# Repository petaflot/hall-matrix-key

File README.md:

# Hall Jumper Selector Matrix

A tool to help getting the configuration of hall sensors correct for any arbitrary 3-phase electric motor fitted with such devices. There are 6 possible arrangements, for direct and inverse rotations, and shifts relative to the phases. A 2x04 matrix is sufficient to select each arrangement by connecting adjacent pins.

A document that gives [more information on the arrangements](hall-jumper-matrix.pdf) can be found here.

## Hall Key

A simple yet elaborate mechanical device to ease the task of finding the correct jumper configuration ; special care was taken to reduce wear on the sliding contacts and thus extend the device life.
It looks pretty and is a somewhat mystical object that you can carry around everywhere you go.

***NOTE: In the above picture, the tracks are wrong ; this was fixed***

Datasheets of the required components are included.

### Note on the circular tracks

Considering the electrical and mechanical constraints, there is a unique solution to the arrangement ; therefore, it can be considered as a rune.

## Hall Matrix

A 2x04 pins jumper configuration matrix ; this project also includes a dedicated a solder jumper matrix footprint for Kicad. The pogo pins of the selector key go there, and they can be soldered once the correct configuration has been found.

***WARNING: footprint is not up-to-date with latest version of key!***

To ensure it can be accessed with the key, this footprint should go at the edge of the board.

An alternative is to use 2x04 header pins and regular jumpers ; this enables the configuration to be changed easily afterwards. In the case, connect to the key with a short cable.

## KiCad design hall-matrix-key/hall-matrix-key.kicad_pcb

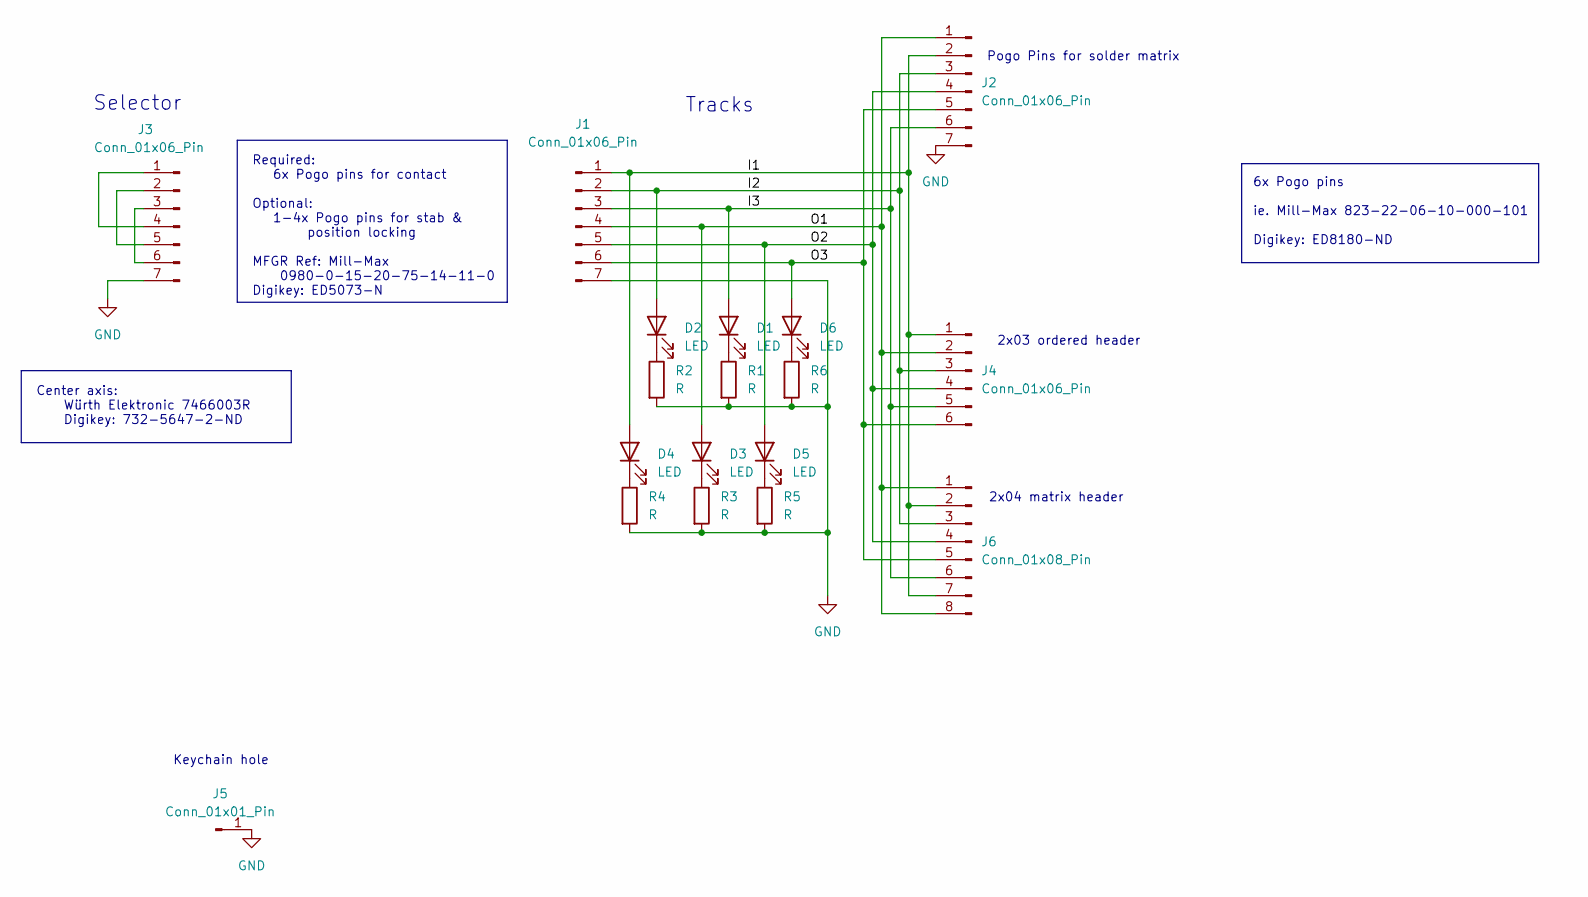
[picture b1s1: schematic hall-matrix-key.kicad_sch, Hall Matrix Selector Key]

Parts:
D1, D2, D3, D4, D5, D6: LED; LED_LiteOn_LTST-S326
J1: Conn_01x06_Pin; hall-matrix-selector-switch_base
J2: Conn_01x06_Pin; hall-matrix-selector_pogo
J3: Conn_01x06_Pin; hall-matrix-selector-switch_knob
J4: Conn_01x06_Pin; PinHeader_2x03_P2.54mm_Vertical
J5: Conn_01x01_Pin; keyhole
J6: Conn_01x08_Pin; PinHeader_2x04_P2.54mm_Vertical
R1, R2, R3, R4, R5, R6: R; R_0805_2012Metric_Pad1.20x1.40mm_HandSolder

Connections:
/I1: D4.2 (A), J1.1, J2.2, J4.1, J6.2, J6.7
/I2: D2.2 (A), J1.2, J2.3, J4.3, J6.3
/I3: D1.2 (A), J1.3, J2.6, J4.5, J6.6
/O1: D3.2 (A), J1.4, J2.1, J4.2, J6.1, J6.8
/O2: D5.2 (A), J1.5, J2.4, J4.4, J6.4
/O3: D6.2 (A), J1.6, J2.5, J4.6, J6.5
GND: J1.7, J2.7, J3.7, J5.1, R1.2, R2.2, R3.2, R4.2, R5.2, R6.2
unnamed: D1.1 (K), R1.1
unnamed: D2.1 (K), R2.1
unnamed: D3.1 (K), R3.1
unnamed: D4.1 (K), R4.1
unnamed: D5.1 (K), R5.1
unnamed: D6.1 (K), R6.1
unnamed: J3.1, J3.4
unnamed: J3.2, J3.5
unnamed: J3.3, J3.6

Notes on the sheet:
Keychain hole
2x03 ordered header
Center axis: Würth Elektronic 7466003R Digikey: 732-5647-2-ND
Pogo Pins for solder matrix
6x Pogo pins ie. Mill-Max 823-22-06-10-000-101 Digikey: ED8180-ND
2x04 matrix header
Selector
Required: 6x Pogo pins for contact Optional: 1-4x Pogo pins for stab & position locking MFGR Ref: Mill-Max 0980-0-15-20-75-14-11-0 Digikey: ED5073-N
Tracks

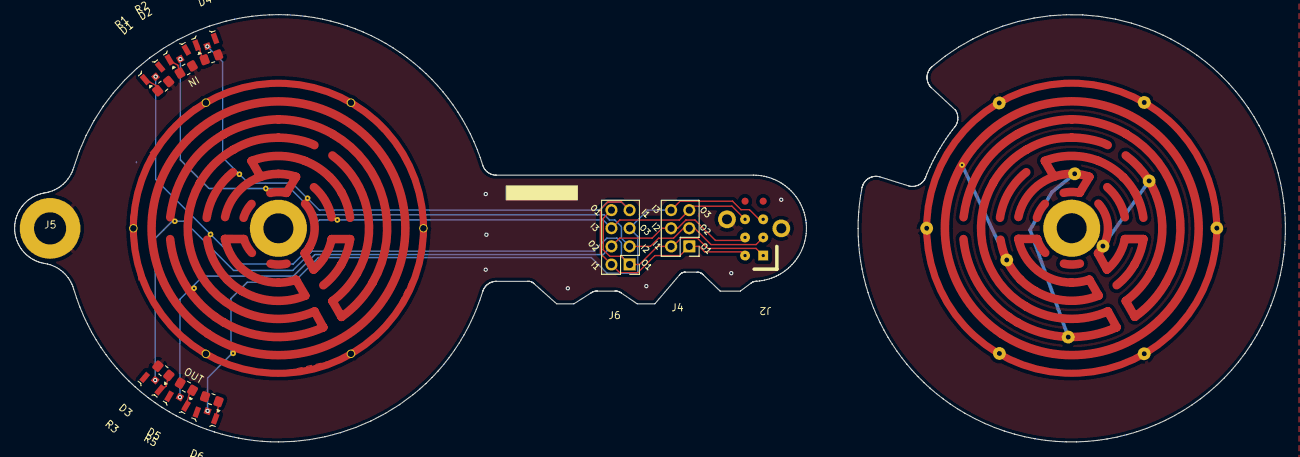
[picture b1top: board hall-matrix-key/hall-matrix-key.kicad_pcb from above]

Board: 2 copper layers, 110.9 x 59.9 mm, 18 parts (0 on the bottom side), 16 nets.

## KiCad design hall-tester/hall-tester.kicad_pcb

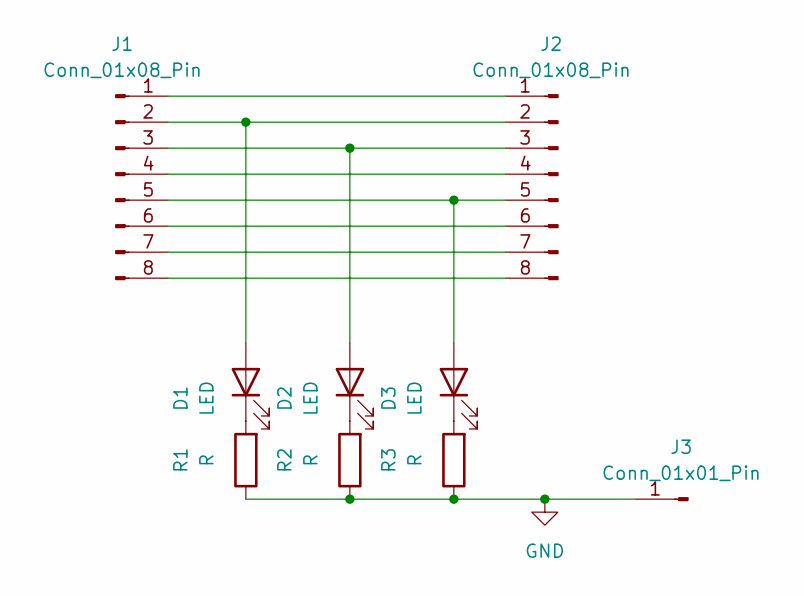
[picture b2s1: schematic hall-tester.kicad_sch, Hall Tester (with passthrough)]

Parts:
D1, D2, D3: LED; LED_Kingbright_APDA3020VBCD
J1: Conn_01x08_Pin; PinHeader_2x04_P2.54mm_Horizontal
J2: Conn_01x08_Pin; EdgeHeader-2.54_2x04
J3: Conn_01x01_Pin; PinHeader_1x01_P2.54mm_Horizontal
R1, R2, R3: R; R_0805_2012Metric_Pad1.20x1.40mm_HandSolder

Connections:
GND: J3.1, R1.1, R2.1, R3.1
unnamed: D1.2 (A), J1.2, J2.2
unnamed: D1.1 (K), R1.2
unnamed: D2.2 (A), J1.3, J2.3
unnamed: D2.1 (K), R2.2
unnamed: D3.2 (A), J1.5, J2.5
unnamed: D3.1 (K), R3.2
unnamed: J1.1, J2.1
unnamed: J1.4, J2.4
unnamed: J1.6, J2.6
unnamed: J1.7, J2.7
unnamed: J1.8, J2.8

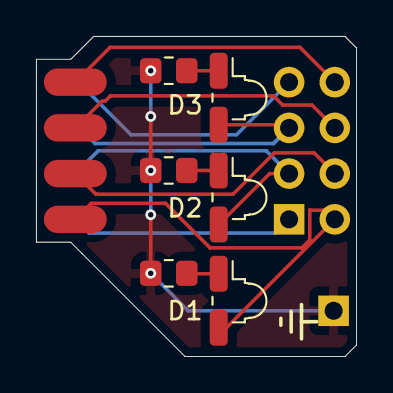
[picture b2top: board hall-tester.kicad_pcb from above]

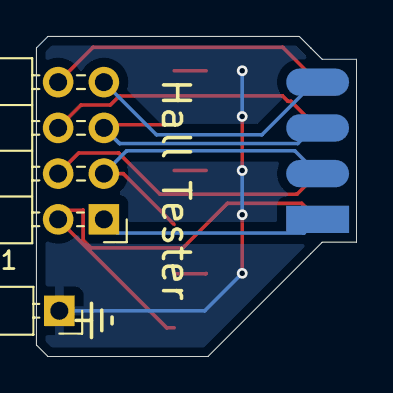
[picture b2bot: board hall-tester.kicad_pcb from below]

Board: 2 copper layers, 17.8 x 17.8 mm, 9 parts (3 on the bottom side), 12 nets.

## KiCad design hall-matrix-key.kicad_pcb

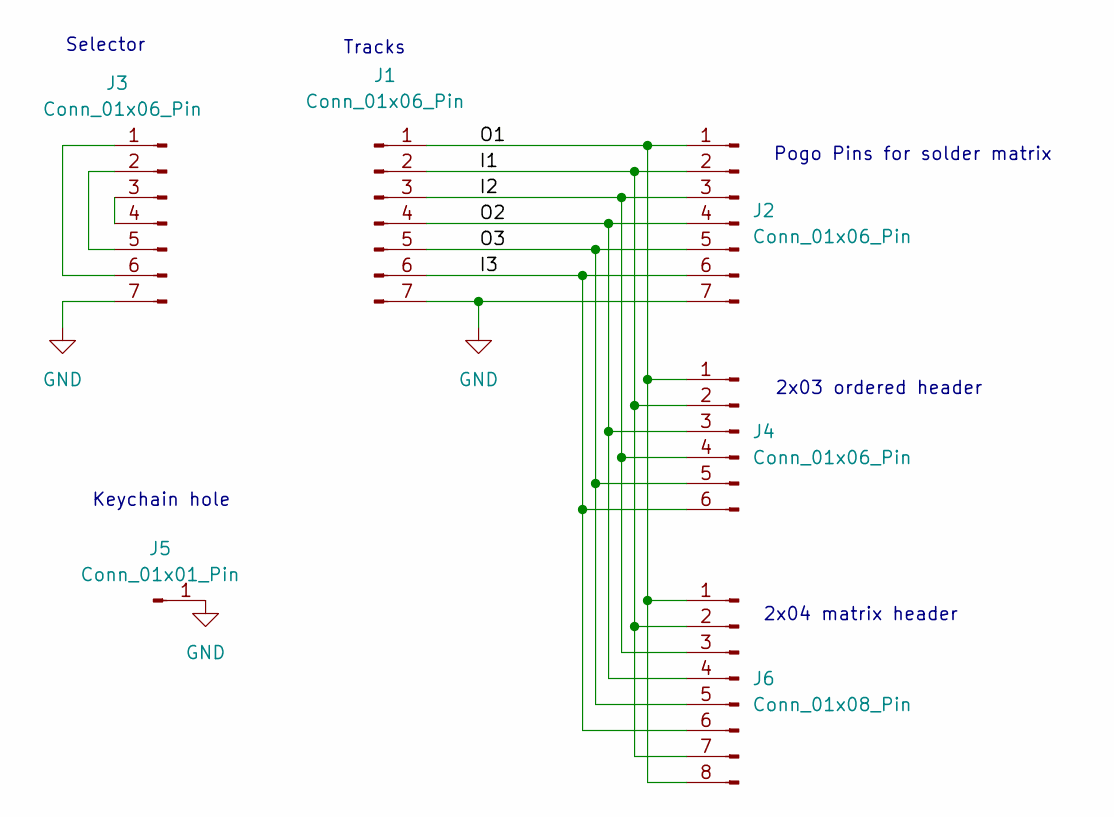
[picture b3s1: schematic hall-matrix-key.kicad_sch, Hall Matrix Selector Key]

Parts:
J1: Conn_01x06_Pin; hall-matrix-selector-switch_base
J2: Conn_01x06_Pin; hall-matrix-selector_pogo
J3: Conn_01x06_Pin; hall-matrix-selector-switch_knob
J4: Conn_01x06_Pin; PinHeader_2x03_P2.54mm_Vertical
J5: Conn_01x01_Pin
J6: Conn_01x08_Pin; PinHeader_2x04_P2.54mm_Vertical

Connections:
/I1: J1.2, J2.2, J4.2, J6.2, J6.7
/I2: J1.3, J2.3, J4.4, J6.3
/I3: J1.6, J2.6, J4.6, J6.6
/O1: J1.1, J2.1, J4.1, J6.1, J6.8
/O2: J1.4, J2.4, J4.3, J6.4
/O3: J1.5, J2.5, J4.5, J6.5
GND: J1.7, J2.7, J3.7, J5.1
unnamed: J3.1, J3.6
unnamed: J3.2, J3.5
unnamed: J3.3, J3.4

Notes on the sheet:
Keychain hole
2x03 ordered header
Pogo Pins for solder matrix
2x04 matrix header
Selector
Tracks

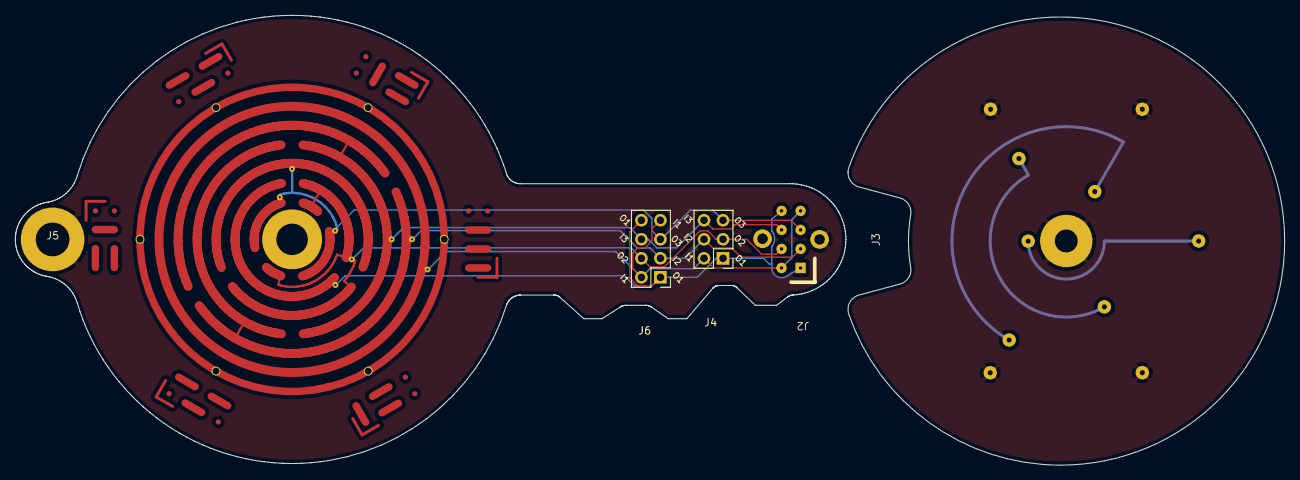
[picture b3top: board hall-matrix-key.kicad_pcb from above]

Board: 2 copper layers, 169.5 x 60.1 mm, 6 parts (0 on the bottom side), 10 nets.

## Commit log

2025-01-03 Ready for fabrication
2025-03-25 stale changes
2025-03-25 doc fix
2025-07-25 second batch with corrections (purple)
2025-07-25 second batch production, should be fixed
    50 (?) pieces ordered for WHY2025, purple/white/ENIG
2025-08-22 update for second, corrected batch.
    series manufactured for WHY2025 have one pogo hole too small on the
    rotator
2025-08-22 link to matrix table
